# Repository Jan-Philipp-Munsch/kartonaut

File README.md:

# Kartonaut

**A cardboard model rocket that steers its own motor.** *Karton* is German for cardboard: the airframe
is a 75 mm cardboard tube, the motor sits in a servo-driven gimbal, and a home-designed flight computer
holds the rocket upright during the burn. Everything from the circuit board to the control gains is
designed, simulated and documented in this repository.

*Deutsche Fassung: [README.de.md](README.de.md) · detailed documents are in German · last updated: 10 Nov 2026*

<table>
<tr>
<td width="50%"></td>
<td width="50%"><br><br>
<b>Flight computer rev B1 has arrived.</b> Left: the board as delivered on 5 Nov 2026, machine-assembled
with 106 parts. Above: the same board as rendered from the KiCad project, which is generated entirely
from a Python description of the circuit. Next step: hand-soldering the Teensy sockets, connectors and
radio, then the bench test.</td>
</tr>
</table>

## From breakout stack to circuit board

**Before:** the first flight computer was a Teensy 4.1 with breakout boards on a printed ring stack,
held together by threaded rods and jumper wires. On it the core functions were proven on the bench:
IMU and gyro offsets, barometer with Kalman altitude, power measurement, SD logging with CSV export,
radio telemetry to the ground, servo control and a pyro channel that fired a test ejection.

**Now:** the mainboard rev B1 carries the same functions on one 54 × 120 mm board, with newer chips:

- **No loose wires.** Plug-in jumper wires were the biggest failure risk in flight; now everything is
  soldered or on locking JST connectors.
- **IMU exactly on the roll axis**, all flight sensors on a fast SPI bus instead of a shared I²C bus.
- **Safe power:** mechanical main switch with FET load switches, a polyfuse per battery, power monitor
  with a Kelvin shunt, charging inside the rocket.
- **LoRa instead of HC-12** for range, plus magnetometer, GPS socket and microSD on board.
- **Room for later flights:** four pyro channels, a fourth servo, a high-g accelerometer footprint and
  a stacking connector.
- **Lighter and smaller:** a printed sled replaces the ring stack, which helped bring the rocket to 704 g.

<br clear="left">

## At a glance

| | *Kartonaut 1* (first flight) |
|---|---|
| Airframe | cardboard tube Ø 75 mm in three screwed modules, 731 mm long, 3D-printed internals |
| Mass | **704 g** lift-off (mass budget, [`cad/mass_stand2b.md`](cad/mass_stand2b.md)), thrust-to-weight 1.7 |
| Motor | TSP E12 (24 mm, 39 Ns, 3.5 s burn) in a two-axis gimbal with 2 × FrSky W5652H servos |
| Flight computer | Teensy 4.1 on a custom 4-layer board: IMU, barometer, magnetometer, power monitor, LoRa 433 MHz, SD, four pyro channels |
| Control | gyro quaternion, PID on pitch and yaw, gains from Bayesian optimisation in a 6DOF simulation |
| Recovery | CO₂ cartridge pushes off the nose cone, 125 cm parachute |
| Predicted flight | about 74 m apogee, tilt below 2.5° during the burn (simulation, no drag) |

## Status

**Done**

- **Gimbal** with both servos built; tubes A and B of the airframe built.
- **Mainboard rev B1** designed as code (Python → KiCad, four layers, DRC clean), reviewed, ordered
  from JLCPCB on 26 Oct and **delivered on 5 Nov 2026**.
- **6DOF simulation** in Python: thrust curve, identified servo dynamics, sensor noise, Monte Carlo;
  it cut the rocket from 981 g to 704 g and found gains that keep the gimbal off its stop.
- **Flight firmware** (state machine, attitude, Kalman altitude, pyro, telemetry, watchdog) and a
  bench-test console for the board, tested in software-in-the-loop against the simulation.
- **Build manual** with drawings and 1:1 drilling templates; launch stand, TVC test rig and the radio
  bridge of the ground station designed in parametric CAD.
- CI on GitHub Actions for firmware, simulation and pin check against the board.

**In review**

- [PR #9](https://github.com/Jan-Philipp-Munsch/kartonaut/pull/9): soldering and measurement guide for
  rev B1, test firmware for the fitted IMU, flight firmware at 250 Hz with PSRAM log and flash flight
  recorder, LoRa antenna build guide.
- [PR #8](https://github.com/Jan-Philipp-Munsch/kartonaut/pull/8): on-board motor ignition through
  pyro 1, triggered by an authenticated radio command from a laptop.

**Next**

1. Hand-solder the board and bench-test it with `revb_test` (power monitor and one resistor follow
   with the second DigiKey shipment).
2. Print and weigh the parts, assemble the rocket, balance the centre of gravity.
3. Ground tests: servo-to-gimbal ratio, CO₂ ejection, TVC test rig with a propeller motor, radio range.
4. ***Kartonaut 1*: controlled ascent on one motor, parachute recovery.**

Details and changelog in [PROJECT.md](PROJECT.md), build log in [docs/BUILD.md](docs/BUILD.md).

## Gallery

<table>
<tr>
<td align="center" width="33%"><br><sub>Section through <i>Kartonaut 1</i>: gimbal, avionics, CO₂ and parachute</sub></td>
<td align="center" width="33%"><br><sub>Push-rod gimbal with two servos, built</sub></td>
<td align="center" width="33%"><br><sub>Avionics module: board on a printed sled</sub></td>
</tr>
<tr>
<td align="center"><br><sub>TVC test rig: a propeller replaces the motor</sub></td>
<td align="center"><br><sub>Launch stand on three adjustable legs</sub></td>
<td align="center"><br><sub>Radio bridge with half-wave dipole</sub></td>
</tr>
<tr>
<td align="center" colspan="2"><br><sub>Simulation: old gains (gimbal saturated) against tuned gains</sub></td>
<td align="center"><br><sub>Overview drawing from the build manual</sub></td>
</tr>
</table>

## What is inside

| Part | What it does | Where |
|---|---|---|
| Mainboard | KiCad project generated from `circuit.py`: schematic, layout, Gerber/BOM/CPL, datasheet | [hardware/mainboard/](hardware/mainboard/README.md) |
| Simulation | Python 6DOF model `tvcsim` with the firmware controller ported 1:1, gain tuning, landing studies | [simulation/](simulation/README.md) |
| Firmware | PlatformIO for Teensy 4.1: flight software, sensor drivers, bench-test console, native tests | [firmware/](firmware/README.md) |
| Mechanics | parametric CAD for printed parts, launch stand, test rig; mass and inertia models | [cad/](cad/README.md) |
| Build manual | modules, parts list, build steps, cable plan ([PDF](docs/bauanleitung/Bauanleitung_Kartonaut1.pdf)) | [docs/Bauanleitung_Kartonaut1.md](docs/Bauanleitung_Kartonaut1.md) |
| Ground system | launch protocol, radio bridge, ESP32 station as later option | [groundstation/](groundstation/README.md) |
| Experiments | ready-to-run ground tests | [docs/experiments/](docs/experiments/README.md) |

```bash
cd simulation && python -m pytest tests            # simulation tests
cd firmware && pio test -e native                  # firmware tests without hardware
cd firmware && pio run -e teensy41_revb            # flight firmware for rev B1
MS_CONFIG=erstflug python cad/modular.py           # printed parts, mass, renders
```

## Background

Inspired by the "Scout F" of [BPS.space](https://bps.space). Later flights may get landing legs, a
landing burn on a second motor and roll control; the board already has room for them. The old ground
station lives in [kartonaut-ground](https://github.com/Jan-Philipp-Munsch/kartonaut-ground).

## License

[MIT](LICENSE). The BPS.space Scout F files that served as reference are not part of this repository.

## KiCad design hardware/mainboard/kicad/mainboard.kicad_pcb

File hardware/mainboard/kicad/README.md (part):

# Mainboard rev B1 – KiCad-Projekt

Stand 2026-10-22. Schaltplan und Platine werden hier **aus Code erzeugt**, nicht von Hand gezeichnet.
Die Quelle der Wahrheit ist `circuit.py`: Schaltplan, Platine und Prüfungen werden daraus abgeleitet.
Die Vorgabe ist die Spezifikation `../README.md`, Stand B1: rev B plus Review A1 bis A8
(`../review_kicad_2026-10-21.md`) und die Entscheidungen E1 bis E10 (`../Komponenten_2026-10-22.md`).
Dieses Dokument beschreibt, wie das Projekt entstanden ist, was fertig ist, was offen ist und wo bewusst
von der Spezifikation abgewichen wurde. Die Fertigerwahl steht in `../Fertiger_2026-10-21.md`.

## 1. Stand auf einen Blick

| Schritt | Stand |
|---|---|
| Schaltung als Daten (`circuit.py`) | 174 Bauteile (12 davon DNP), 114 Netze, 7 Schaltplanblätter |
| ERC | **0 Fehler, 0 Warnungen**, 4 begründete Ausschlüsse (§6) |
| Netzliste gegen Spezifikation §4 (`check_design.py`) | **OK**: 39 Teensy-Pins, 7 Chip-Selects, 7 Mux-Kanäle, 11 Schienen, Kelvin-Abgriff |
| Platzierung | **alle 174 Footprints**, keine Überschneidung; die drei Sensoren vom 23.10. mit `add_parts.py` nachgesetzt |
| Strompfade | 2S-Pfad, Pyro-Ausgänge und VSYS_IN als F.Cu-Flächen (§5.4); kein 2S-Netz auf In2 |
| Routing | 3145 Bahnsegmente, 469 Vias, vier Lagen (Stand 24.10.); `./make.sh pcb` braucht etwa 25 Minuten, danach `close_gaps.py` (§5.5) |
| DRC (JLC-Regeln) | **0 Fehler**, Schaltplan-Parität **0 Abweichungen** |
| Offene Verbindungen | **0** (23.10., nach Handrouting und Skript-Router) |
| Abbildungen | Renders oben, unten und schräg, Lagenbilder (`img/`) |
| Rundgang | `RUNDGANG_PLATINE.pdf`: Anleitung mit Bildern zu Aufbau, Lagen, Strompfaden, Vias und DRC (`guide_dump.py`, `make_guide.py`) |
| Fertigungsdaten (Gerber, BOM, CPL) | `./make.sh fab` → `fab/`, Stand 23.10. mit den drei Sensoren (§8) |

| Oben | Unten |
|---|---|
|  |  |

Die Lagen einzeln: `img/layers.pdf` (F.Cu, In1 GND, In2, B.Cu Versorgung, Bestückungsdruck) und
`img/layer_*.png`.

## 2. Werkzeuge

- **KiCad 10.0.6.** Die winget-Installation für alle Benutzer blieb an der Administrator-Abfrage
  hängen. Deshalb wurde der signierte Installer (KiCad Services Corp.) als Benutzerinstallation
  ausgeführt: `/S /CurrentUser` nach `%LOCALAPPDATA%\Programs\KiCad\10.0`. Die globalen
  Bibliothekstabellen (`sym-lib-table`, `fp-lib-table`) wurden aus dem Template nach
  `%APPDATA%\kicad\10.0\` kopiert; das macht die GUI sonst beim ersten Start.
- **easyeda2kicad** (pip) für die Teile, die nicht in der KiCad-Bibliothek sind: LSM6DSV16X (C5267406, Symbol; der Footprint ist der des ICM-42688-P C1850418, gleiches Land-Pattern),
  BMP390 (C5124834), TPS63070RNMR (C109322) und E22-400T22S (C2903765). Symbol, Footprint und
  3D-Modell kommen direkt aus der LCSC/EasyEDA-Datenbank, also genau die Footprints, mit denen JLC bestückt.
- **Freerouting 2.5.0** als JAR mit einer portablen **Temurin-25-JRE** (Zip, keine Installation), beides
  unter `%LOCALAPPDATA%\Programs\freerouting\`, Prüfsummen kontrolliert. Die native
  `freerouting-cli.exe` derselben Version stürzt mit einem GraalVM-Fehler ab; die JAR braucht Java 25.
- **CadQuery** für zwei 3D-Modelle, die fehlen: Teensy 4.1 (vereinfacht, auf 8,5-mm-Sockeln) und
  XT30PW-M (die KiCad-Bibliothek nennt das Modell, liefert es aber nicht).
- Datenblätter für die eigenen Entscheidungen: TPS63070 (SLVSC58B: Pinbelegung, Teiler-Tabelle 4,
  Kondensatoren), ICM-42688-P (DS-000347) und LSM6DSV16X (AN5763 Tab. 1: Pins 9–11 offen, 2–3 an GND).

## 3. Aufbau und Ablauf

```
circuit.py          Schaltung als Daten: Bauteile, Werte, Footprints, LCSC-Nummern, Netze, Blätter, Blöcke, Netzklassen
build_lib.py        lib/mainboard.*: Teensy-Symbol, INA239-Symbol, Sockel-Footprint, Kelvin-Shunt-Footprint
                    R_2512_Kelvin, 3D-Modelle Teensy und XT30; Pin-Typen der LCSC-Symbole
gen_schematic.py    Projektdatei (JLC-Regeln, Netzklassen, ERC-Ausschlüsse), Wurzelblatt und 7 Unterblätter
check_design.py     Tor 1: Netzliste aus dem Schaltplan gegen die Pin-Tabelle der Spezifikation
gen_pcb.py          Platine: Umriss, Footprints, Platzierung, Flächen, Sperrflächen, Plane-Vias, DSN-Export, SES-Übernahme, Nachbesserung,
                    Bestückungsdruck (`gen_pcb.py silk`: nur der Druck, auf der gerouteten Platine)
logo.py             Kartonaut-Abzeichen als Polygone, für den Bestückungsdruck und docs/brand/*.svg
render.py           Lagenbilder zuschneiden und zusammenfügen, Renders auf die Platine zuschneiden
make.sh             ganze Kette: ./make.sh [sch|pcb|drc|img|fab]
fab.py              `./make.sh fab`: Bestelldateien für JLCPCB nach fab/ (Gerber/Bohrdaten als ZIP, BOM, CPL, FAB.md)
widen.py            verbreitert schmale Versorgungsstücke, soweit der DRC es zulässt (nach dem Handrouting)
add_parts.py        setzt neue Bauteile aus circuit.py an feste Positionen in die fertige Platine (Netze, Blattpfad, DNP),
                    räumt fremdes Kupfer unter ihren Pads weg; danach close_gaps.py / route_gaps.py
snapshot.py         schnelles Bild einzelner Lagen beim Entwickeln
gaps.py             die offenen Verbindungen aus out/drc.json: was, wo, wie weit; `gaps.py png` mit Bild je Häufung
close_gaps.py       `dump`: Geometrie der Platine und die offenen Verbindungen nach out/geom.json; `apply`: Ergebnis des
                    Gitter-Routers in die Platine (KiCad-Python)
route_gaps.py       Gitter-Router (System-Python mit numpy/scipy): A* auf 0,05 mm, F.Cu/In2 mit Vias, Rip-up von
                    Signalbahnen; `debug n` mit Bild und Kennzahlen je Lücke, `region x0 y0 x1 y1` reißt einen Bereich auf
lib/                lcsc.* (easyeda2kicad), mainboard.* (eigene)
out/                Schaltplan-PDF, ERC- und DRC-Bericht (alles andere dort ist Zwischenstand)
img/                Renders und Lagenbilder
fab/                Bestelldateien (ZIP, BOM, CPL, FAB.md); fab/gerber/ ist der ungepackte Zwischenstand
```

Neu erzeugen (Git Bash):

```bash
./make.sh
```

`make.sh` ruft `kicad-cli` aus der Bash auf und nicht aus Python. Aus der Microsoft-Store-Python gestartet,
findet `kicad-cli` die globalen Bibliothekstabellen nicht, denn der App-Container der Store-Python
verdeckt sie. Der ERC meldet dann 265 Bibliotheksfehler, und die Renders haben keine Modelle.

Warum Code statt GUI: Schaltung, Schaltplan und Platine können nicht auseinanderlaufen, jede Änderung ist
ein Diff in `circuit.py`, und ERC, Netzlistenprüfung und DRC laufen auf Knopfdruck. Die Dateien lassen sich
normal in KiCad öffnen. Sobald dort von Hand geroutet wird (§5.4), ist die Platinendatei die Quelle und
`./make.sh pcb` darf nicht mehr laufen. `./make.sh sch` und `./make.sh drc` bleiben nutzbar.

## 4. Schaltplan

Jedes Pin bekommt einen kurzen Draht und ein globales Netzlabel. So sind die Netznamen in Netzliste,
Platine, Netzklassen und Spezifikation dieselben (`VSERVO`, nicht `/Versorgung/VSERVO`). Jedes Blatt
ist in umrahmte Funktionsblöcke gegliedert. Die Blätter heißen Versorgung, Teensy, Sensorik, Funk,
Aktoren, Pyro und Signal. Die UUIDs werden aus Blatt und Referenz berechnet und sind deshalb bei jedem
Lauf gleich. PDF: `out/mainboard_schematic.pdf`.

## 5. Platine

### 5.1 Lagen

| Lage | Inhalt |
|---|---|
| F.Cu | alle Bauteile, Signale, GND-Füllung |
| In1.Cu | **durchgehende GND-Fläche** (Lagentyp *power*, wird nicht geroutet) |
| In2.Cu | Signale, GND-Füllung |
| B.Cu | **geteilte Versorgungsfläche**: GND_PWR unter allem, was am 2S hängt (TVC-Band mit XT30 und Servos, Mitte unter den VSERVO-Puffern, rechter Streifen mit den Aktoren, äußerer rechter Streifen neben J_STACK, Spitzen-Band unter Pyro, Arming und Summer); **5V_SYS** unter der 1S-Seite (linker Streifen, unter dem Teensy) |

Die Spezifikation sah die Versorgungsflächen auf Lage 3 vor. B.Cu ist gleichwertig und trägt ohnehin
keine Bauteile. In2 bleibt so als zweite Signallage frei; ohne sie war die Platine nicht zu entflechten.
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
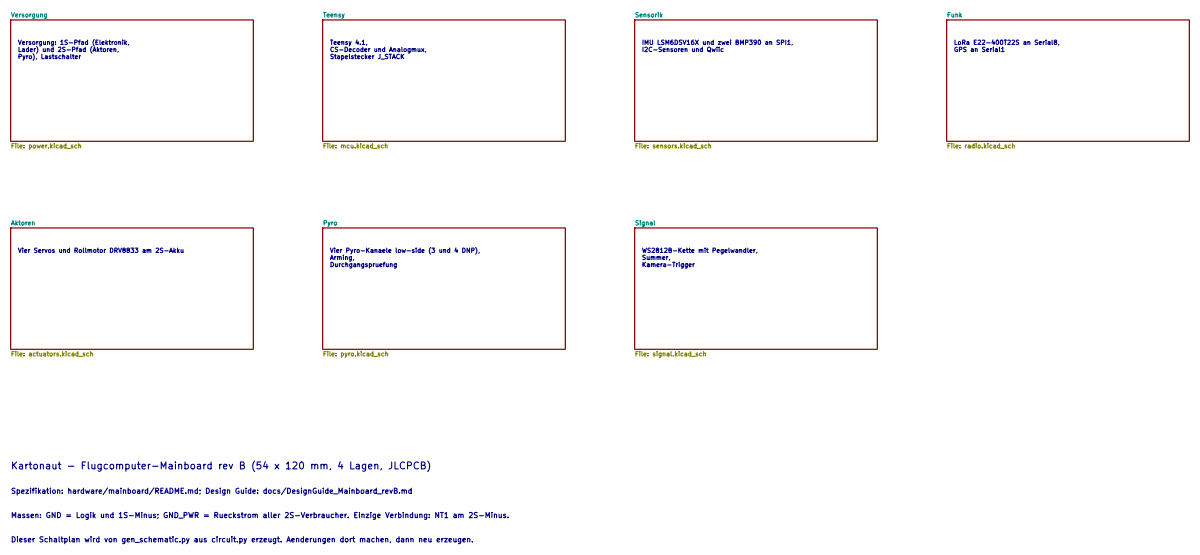
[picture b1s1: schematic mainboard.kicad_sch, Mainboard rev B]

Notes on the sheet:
Versorgung: 1S-Pfad (Elektronik, Lader) und 2S-Pfad (Aktoren, Pyro), Lastschalter
Teensy 4.1, CS-Decoder und Analogmux, Stapelstecker J_STACK
IMU LSM6DSV16X und zwei BMP390 an SPI1, I2C-Sensoren und Qwiic
LoRa E22-400T22S an Serial8, GPS an Serial1
Vier Servos und Rollmotor DRV8833 am 2S-Akku
Vier Pyro-Kanaele low-side (3 und 4 DNP), Arming, Durchgangspruefung
WS2812B-Kette mit Pegelwandler, Summer, Kamera-Trigger
Kartonaut - Flugcomputer-Mainboard rev B (54 x 120 mm, 4 Lagen, JLCPCB)
Spezifikation: hardware/mainboard/README.md; Design Guide: docs/DesignGuide_Mainboard_revB.md
Massen: GND = Logik und 1S-Minus; GND_PWR = Rueckstrom aller 2S-Verbraucher. Einzige Verbindung: NT1 am 2S-Minus.
Dieser Schaltplan wird von gen_schematic.py aus circuit.py erzeugt. Aenderungen dort machen, dann neu erzeugen.

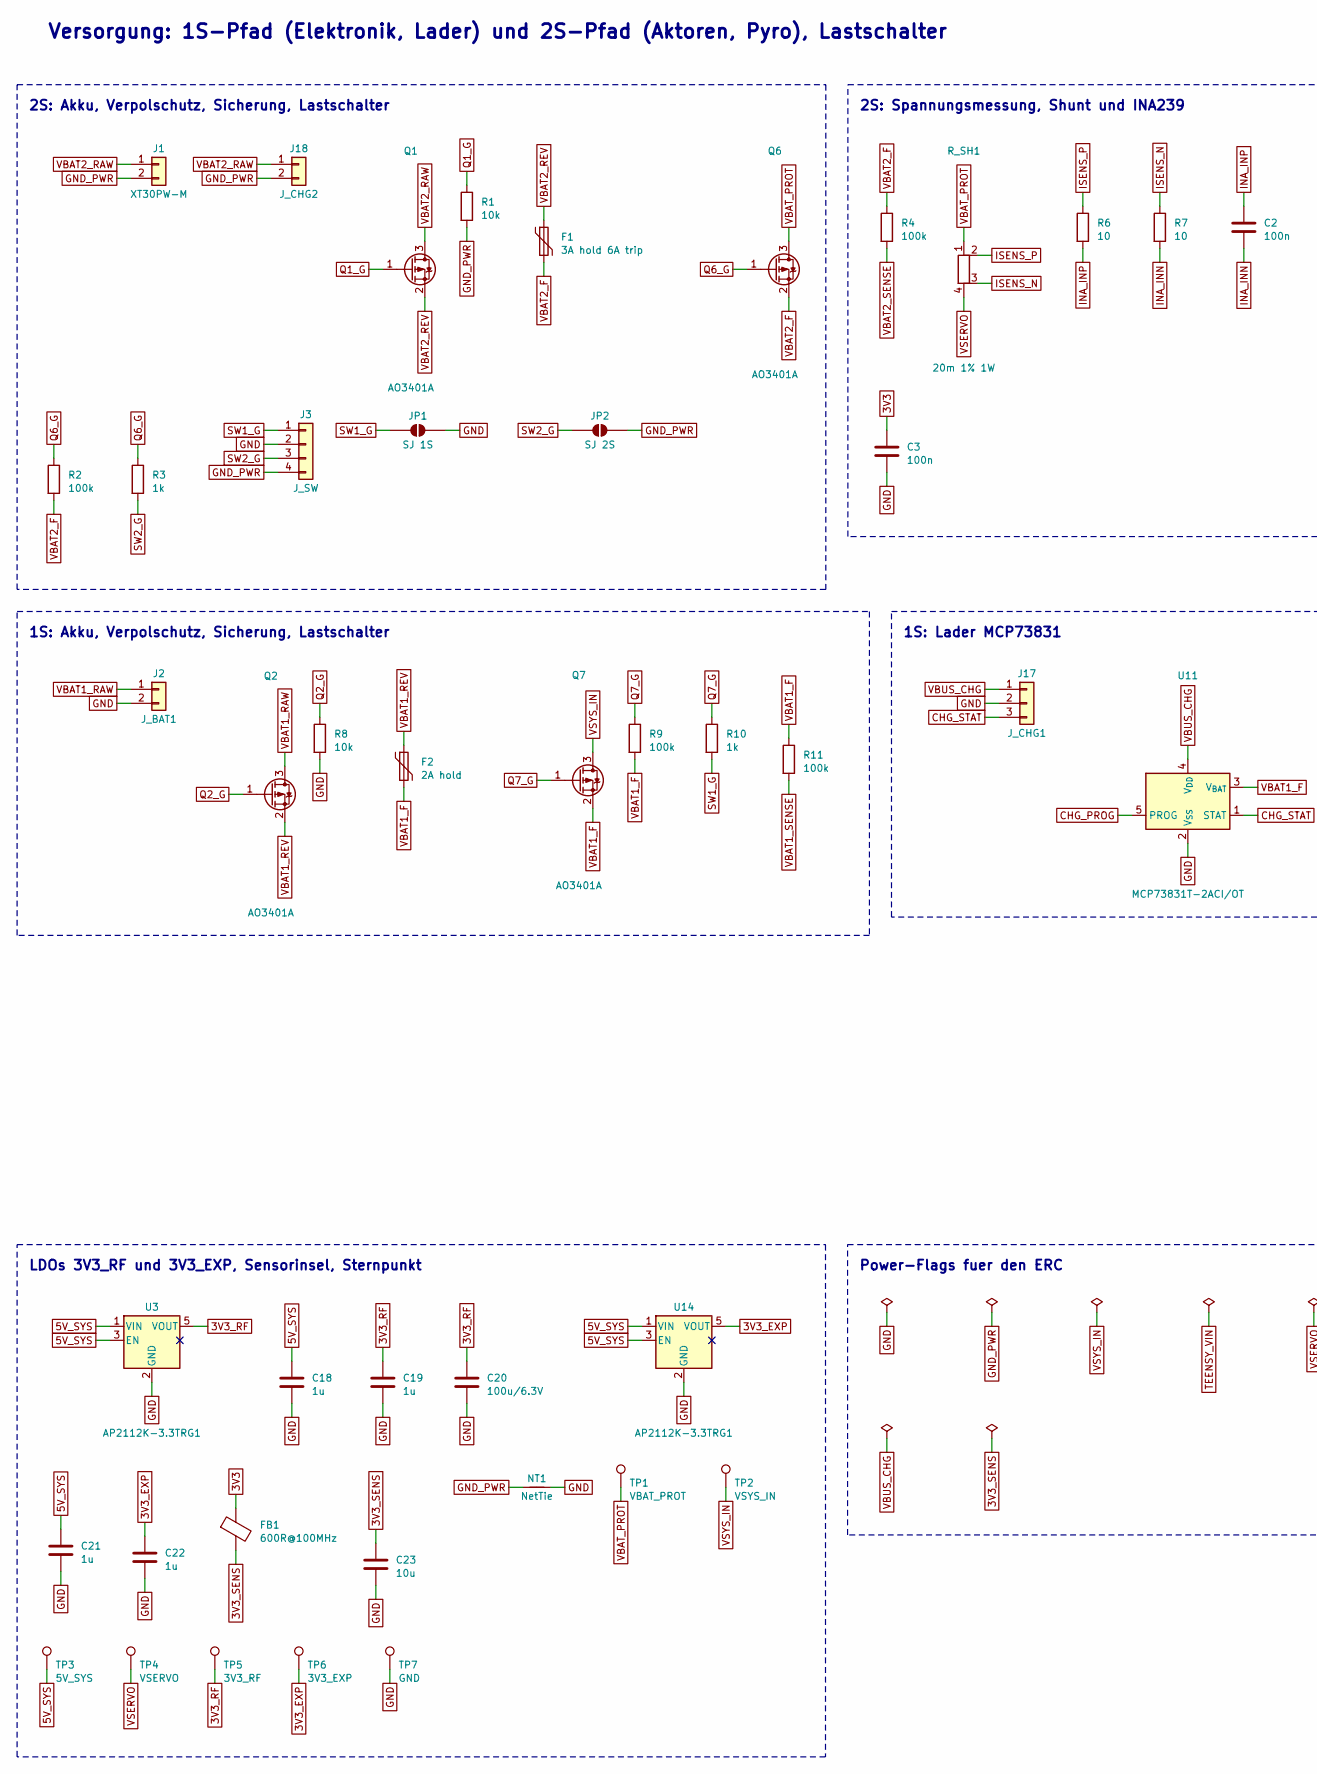
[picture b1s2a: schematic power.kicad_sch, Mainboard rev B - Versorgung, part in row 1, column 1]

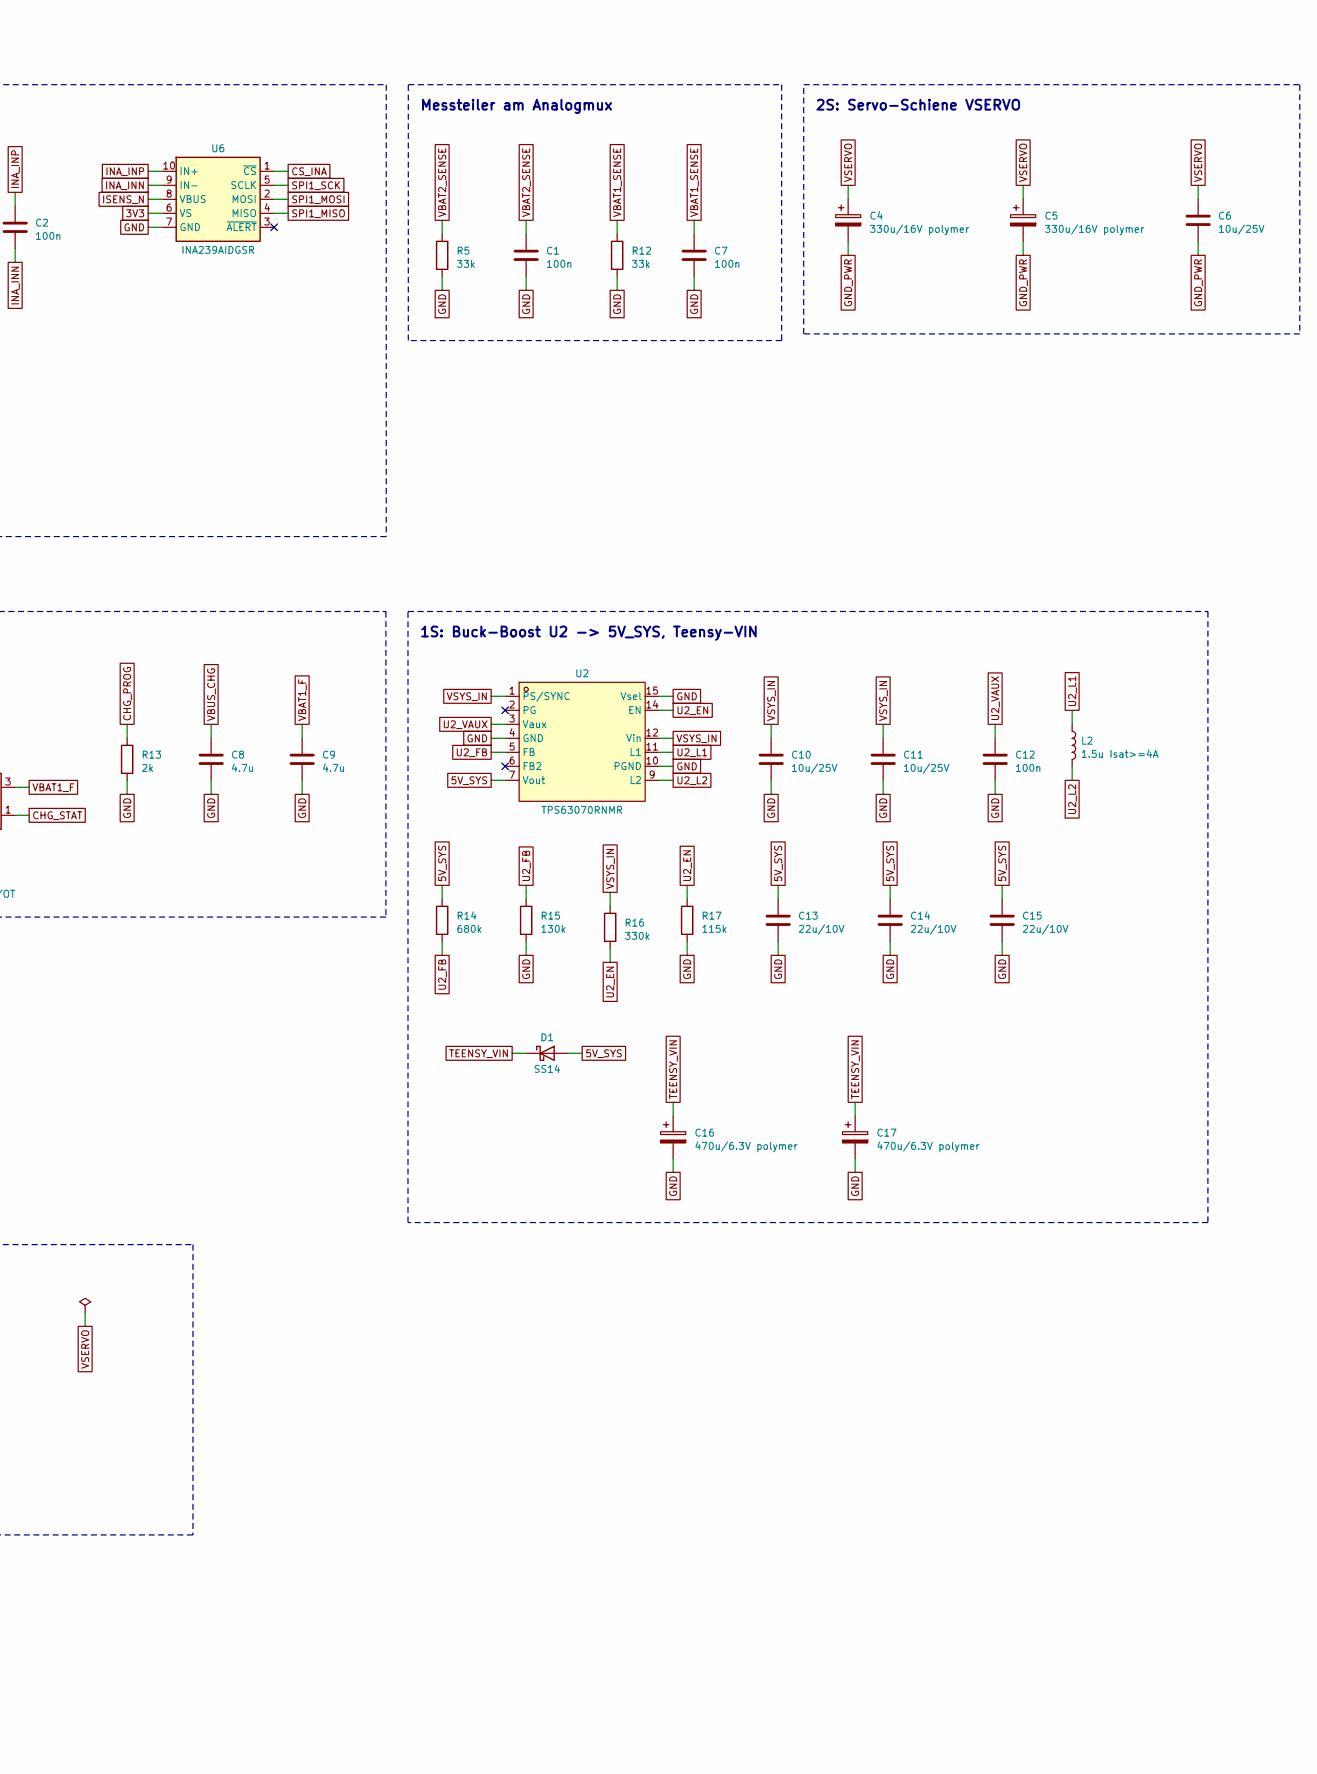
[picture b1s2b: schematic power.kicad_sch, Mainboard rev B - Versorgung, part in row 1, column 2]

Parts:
C1, C2, C3, C7, C12: 100n; C_0603_1608Metric
C4, C5: 330u/16V polymer; CP_EIA-7343-31_Kemet-D
C6, C10, C11: 10u/25V; C_0805_2012Metric
C8, C9: 4.7u; C_0805_2012Metric
C13, C14, C15: 22u/10V; C_0805_2012Metric
C16, C17: 470u/6.3V polymer; CP_EIA-7343-31_Kemet-D
C18, C19, C21, C22: 1u; C_0603_1608Metric
C20: 100u/6.3V; C_1210_3225Metric
C23: 10u; C_0805_2012Metric
D1: SS14; D_SMA; LCSC C2480
F1: 3A hold 6A trip; Fuse_1812_4532Metric
F2: 2A hold; Fuse_1812_4532Metric
FB1: 600R@100MHz; L_0603_1608Metric
J1: XT30PW-M; AMASS_XT30PW-M_1x02_P2.50mm_Horizontal
J2: J_BAT1; JST_PH_B2B-PH-K_1x02_P2.00mm_Vertical
J3: J_SW; JST_PH_B4B-PH-K_1x04_P2.00mm_Vertical
J17: J_CHG1; JST_PH_B3B-PH-K_1x03_P2.00mm_Vertical
J18: J_CHG2; JST_PH_B2B-PH-K_1x02_P2.00mm_Vertical
JP1: SJ 1S; SolderJumper-2_P1.3mm_Open_RoundedPad1.0x1.5mm
JP2: SJ 2S; SolderJumper-2_P1.3mm_Open_RoundedPad1.0x1.5mm
L2: 1.5u Isat>=4A; L_Changjiang_FNR5040S
NT1: NetTie; NetTie-2_SMD_Pad0.5mm
Q1, Q2, Q6, Q7: AO3401A; SOT-23; LCSC C15127
R1, R8: 10k; R_0603_1608Metric
R2, R4, R9, R11: 100k; R_0603_1608Metric
R3, R10: 1k; R_0603_1608Metric
R5, R12: 33k; R_0603_1608Metric
R6, R7: 10; R_0603_1608Metric
R13: 2k; R_0603_1608Metric
R14: 680k; R_0603_1608Metric
R15: 130k; R_0603_1608Metric
R16: 330k; R_0603_1608Metric
R17: 115k; R_0603_1608Metric
R_SH1: 20m 1% 1W; R_2512_Kelvin
TP1: VBAT_PROT; TestPoint_Pad_D1.5mm
TP2: VSYS_IN; TestPoint_Pad_D1.5mm
TP3: 5V_SYS; TestPoint_Pad_D1.5mm
TP4: VSERVO; TestPoint_Pad_D1.5mm
TP5: 3V3_RF; TestPoint_Pad_D1.5mm
TP6: 3V3_EXP; TestPoint_Pad_D1.5mm
TP7: GND; TestPoint_Pad_D1.5mm
U2: TPS63070RNMR; VQFN-15_L3.0-W2.5-P0.50-BL; LCSC C109322
U3, U14: AP2112K-3.3TRG1; SOT-23-5; LCSC C51118
U6: INA239AIDGSR; MSOP-10_3x3mm_P0.5mm
U11: MCP73831T-2ACI/OT; SOT-23-5; LCSC C424093

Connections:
3V3: C3.1, FB1.1, U6.6 (VS); also elsewhere on the board
3V3_EXP: C22.1, TP6.1, U14.5 (VOUT); also elsewhere on the board
3V3_RF: C19.1, C20.1, TP5.1, U3.5 (VOUT); also elsewhere on the board
3V3_SENS: C23.1, FB1.2; also elsewhere on the board
5V_SYS: C13.1, C14.1, C15.1, C18.1, C21.1, D1.2 (A), R14.1, TP3.1, U2.7 (Vout), U3.1 (VIN), U3.3 (EN), U14.1 (VIN), U14.3 (EN); also elsewhere on the board
CHG_PROG: R13.1, U11.5 (PROG)
CHG_STAT: J17.3, U11.1 (STAT)
CS_INA: U6.1 (~CS); also elsewhere on the board
GND: C1.2, C3.2, C7.2, C8.2, C9.2, C10.2, C11.2, C12.2, C13.2, C14.2, C15.2, C16.2, C17.2, C18.2, C19.2, C20.2, C21.2, C22.2, C23.2, J2.2, J3.2, J17.2, JP1.2 (B), NT1.2, R5.2, R8.2, R12.2, R13.2, R15.2, R17.2, TP7.1, U2.4 (GND), U2.10 (PGND), U2.15 (Vsel), U3.2 (GND), U6.7 (GND), U11.2 (V_{SS}), U14.2 (GND); also elsewhere on the board
GND_PWR: C4.2, C5.2, C6.2, J1.2, J3.4, J18.2, JP2.2 (B), NT1.1, R1.2; also elsewhere on the board
INA_INN: C2.2, R7.2, U6.9 (IN-)
INA_INP: C2.1, R6.2, U6.10 (IN+)
ISENS_N: R7.1, R_SH1.3, U6.8 (VBUS)
ISENS_P: R6.1, R_SH1.2
Q1_G: Q1.1 (G), R1.1
Q2_G: Q2.1 (G), R8.1
Q6_G: Q6.1 (G), R2.1, R3.1
Q7_G: Q7.1 (G), R9.1, R10.1
SPI1_MISO: U6.4 (MISO); also elsewhere on the board
SPI1_MOSI: U6.2 (MOSI); also elsewhere on the board
SPI1_SCK: U6.5 (SCLK); also elsewhere on the board
SW1_G: J3.1, JP1.1 (A), R10.2
SW2_G: J3.3, JP2.1 (A), R3.2
TEENSY_VIN: C16.1, C17.1, D1.1 (K); also elsewhere on the board
U2_EN: R16.2, R17.1, U2.14 (EN)
U2_FB: R14.2, R15.1, U2.5 (FB)
U2_L1: L2.1, U2.11 (L1)
U2_L2: L2.2, U2.9 (L2)
U2_VAUX: C12.1, U2.3 (Vaux)
VBAT1_F: C9.1, F2.2, Q7.2 (S), R9.2, R11.1, U11.3 (V_{BAT})
VBAT1_RAW: J2.1, Q2.3 (D)
VBAT1_REV: F2.1, Q2.2 (S)
VBAT1_SENSE: C7.1, R11.2, R12.1; also elsewhere on the board
VBAT2_F: F1.2, Q6.2 (S), R2.2, R4.1
VBAT2_RAW: J1.1, J18.1, Q1.3 (D)
VBAT2_REV: F1.1, Q1.2 (S)
VBAT2_SENSE: C1.1, R4.2, R5.1; also elsewhere on the board
VBAT_PROT: Q6.3 (D), R_SH1.1, TP1.1; also elsewhere on the board
VBUS_CHG: C8.1, J17.1, U11.4 (V_{DD})
VSERVO: C4.1, C5.1, C6.1, R_SH1.4, TP4.1; also elsewhere on the board
VSYS_IN: C10.1, C11.1, Q7.3 (D), R16.1, TP2.1, U2.1 (PS/SYNC), U2.12 (Vin)

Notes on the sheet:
Versorgung: 1S-Pfad (Elektronik, Lader) und 2S-Pfad (Aktoren, Pyro), Lastschalter
2S: Akku, Verpolschutz, Sicherung, Lastschalter
2S: Spannungsmessung, Shunt und INA239
Messteiler am Analogmux
2S: Servo-Schiene VSERVO
1S: Akku, Verpolschutz, Sicherung, Lastschalter
1S: Lader MCP73831
1S: Buck-Boost U2 -> 5V_SYS, Teensy-VIN
LDOs 3V3_RF und 3V3_EXP, Sensorinsel, Sternpunkt
Power-Flags fuer den ERC

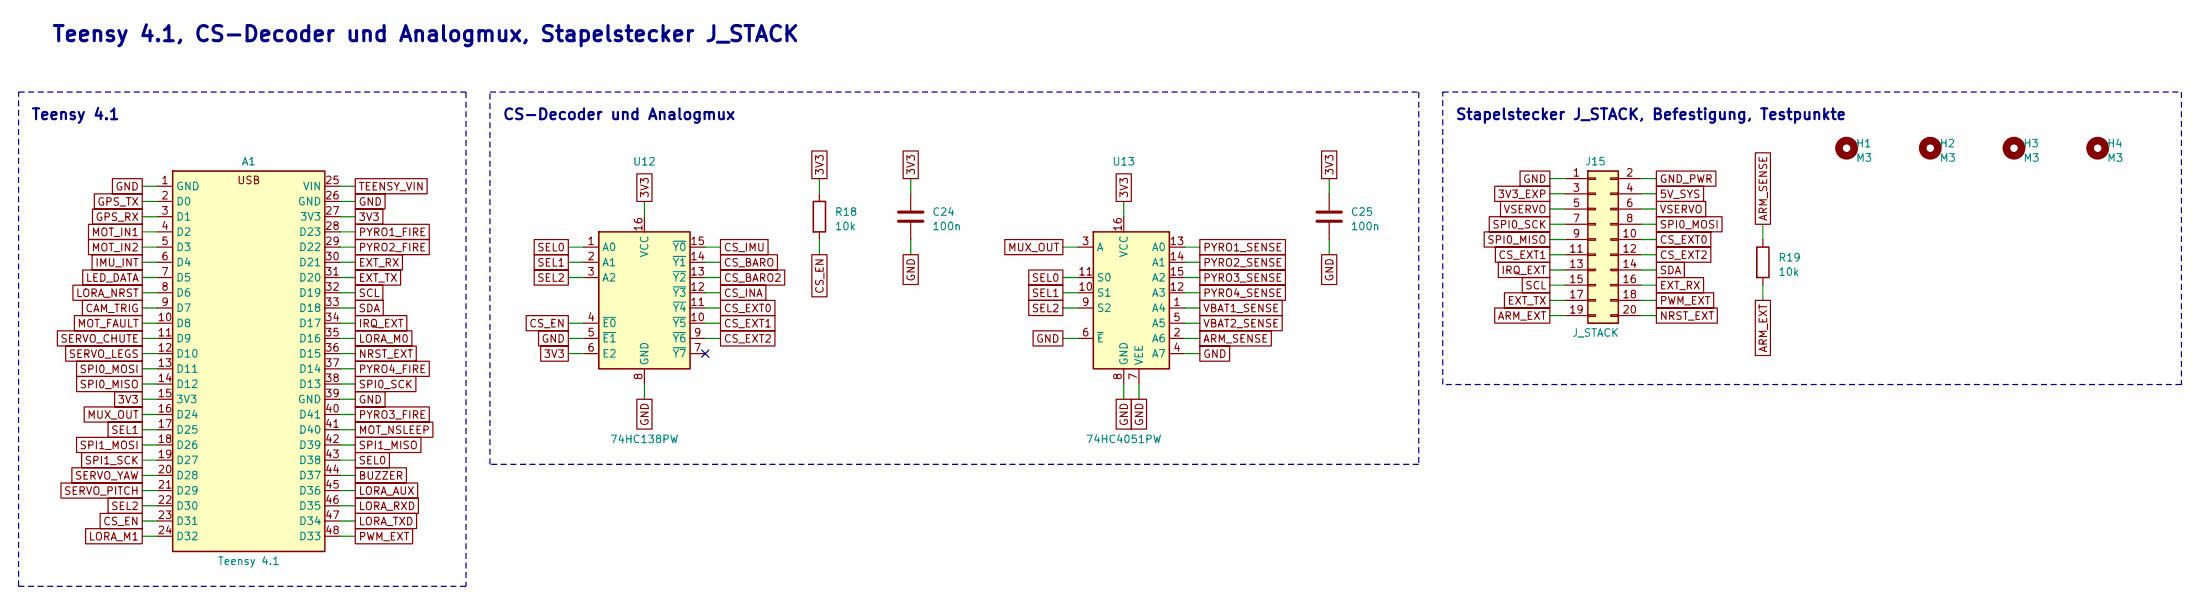
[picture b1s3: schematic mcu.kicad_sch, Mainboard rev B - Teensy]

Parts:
A1: Teensy 4.1; Teensy41_Socket
C24, C25: 100n; C_0603_1608Metric
H1, H2, H3, H4: M3; MountingHole_3.2mm_M3
J15: J_STACK; PinHeader_2x10_P2.54mm_Vertical
R18, R19: 10k; R_0603_1608Metric
U12: 74HC138PW; TSSOP-16_4.4x5mm_P0.65mm
U13: 74HC4051PW; TSSOP-16_4.4x5mm_P0.65mm

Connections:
3V3: A1.15 (3V3), A1.27 (3V3), C24.1, C25.1, R18.1, U12.6 (E2), U12.16 (VCC), U13.16 (VCC); also elsewhere on the board
3V3_EXP: J15.3; also elsewhere on the board
5V_SYS: J15.4; also elsewhere on the board
ARM_EXT: J15.19, R19.2
ARM_SENSE: R19.1, U13.2 (A6); also elsewhere on the board
BUZZER: A1.44 (D37); also elsewhere on the board
CAM_TRIG: A1.9 (D7); also elsewhere on the board
CS_BARO: U12.14 (~Y1); also elsewhere on the board
CS_BARO2: U12.13 (~Y2); also elsewhere on the board
CS_EN: A1.23 (D31), R18.2, U12.4 (~E0)
CS_EXT0: J15.10, U12.11 (~Y4)
CS_EXT1: J15.11, U12.10 (~Y5)
CS_EXT2: J15.12, U12.9 (~Y6)
CS_IMU: U12.15 (~Y0); also elsewhere on the board
CS_INA: U12.12 (~Y3); also elsewhere on the board
EXT_RX: A1.30 (D21), J15.16
EXT_TX: A1.31 (D20), J15.17
GND: A1.1 (GND), A1.26 (GND), A1.39 (GND), C24.2, C25.2, J15.1, U12.5 (~E1), U12.8 (GND), U13.4 (A7), U13.6 (~E), U13.7 (VEE), U13.8 (GND); also elsewhere on the board
GND_PWR: J15.2; also elsewhere on the board
GPS_RX: A1.3 (D1); also elsewhere on the board
GPS_TX: A1.2 (D0); also elsewhere on the board
IMU_INT: A1.6 (D4); also elsewhere on the board
IRQ_EXT: A1.34 (D17), J15.13
LED_DATA: A1.7 (D5); also elsewhere on the board
LORA_AUX: A1.45 (D36); also elsewhere on the board
LORA_M0: A1.35 (D16); also elsewhere on the board
LORA_M1: A1.24 (D32); also elsewhere on the board
LORA_NRST: A1.8 (D6); also elsewhere on the board
LORA_RXD: A1.46 (D35); also elsewhere on the board
LORA_TXD: A1.47 (D34); also elsewhere on the board
MOT_FAULT: A1.10 (D8); also elsewhere on the board
MOT_IN1: A1.4 (D2); also elsewhere on the board
MOT_IN2: A1.5 (D3); also elsewhere on the board
MOT_NSLEEP: A1.41 (D40); also elsewhere on the board
MUX_OUT: A1.16 (D24), U13.3 (A)
NRST_EXT: A1.36 (D15), J15.20
PWM_EXT: A1.48 (D33), J15.18
PYRO1_FIRE: A1.28 (D23); also elsewhere on the board
PYRO1_SENSE: U13.13 (A0); also elsewhere on the board
PYRO2_FIRE: A1.29 (D22); also elsewhere on the board
PYRO2_SENSE: U13.14 (A1); also elsewhere on the board
PYRO3_FIRE: A1.40 (D41); also elsewhere on the board
PYRO3_SENSE: U13.15 (A2); also elsewhere on the board
PYRO4_FIRE: A1.37 (D14); also elsewhere on the board
PYRO4_SENSE: U13.12 (A3); also elsewhere on the board
SCL: A1.32 (D19), J15.15; also elsewhere on the board
SDA: A1.33 (D18), J15.14; also elsewhere on the board
SEL0: A1.43 (D38), U12.1 (A0), U13.11 (S0)
SEL1: A1.17 (D25), U12.2 (A1), U13.10 (S1)
SEL2: A1.22 (D30), U12.3 (A2), U13.9 (S2)
SERVO_CHUTE: A1.11 (D9); also elsewhere on the board
SERVO_LEGS: A1.12 (D10); also elsewhere on the board
SERVO_PITCH: A1.21 (D29); also elsewhere on the board
SERVO_YAW: A1.20 (D28); also elsewhere on the board
SPI0_MISO: A1.14 (D12), J15.9
SPI0_MOSI: A1.13 (D11), J15.8
SPI0_SCK: A1.38 (D13), J15.7
SPI1_MISO: A1.42 (D39); also elsewhere on the board
SPI1_MOSI: A1.18 (D26); also elsewhere on the board
SPI1_SCK: A1.19 (D27); also elsewhere on the board
TEENSY_VIN: A1.25 (VIN); also elsewhere on the board
VBAT1_SENSE: U13.1 (A4); also elsewhere on the board
VBAT2_SENSE: U13.5 (A5); also elsewhere on the board
VSERVO: J15.5, J15.6; also elsewhere on the board

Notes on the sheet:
Teensy 4.1, CS-Decoder und Analogmux, Stapelstecker J_STACK
Teensy 4.1
CS-Decoder und Analogmux
Stapelstecker J_STACK, Befestigung, Testpunkte

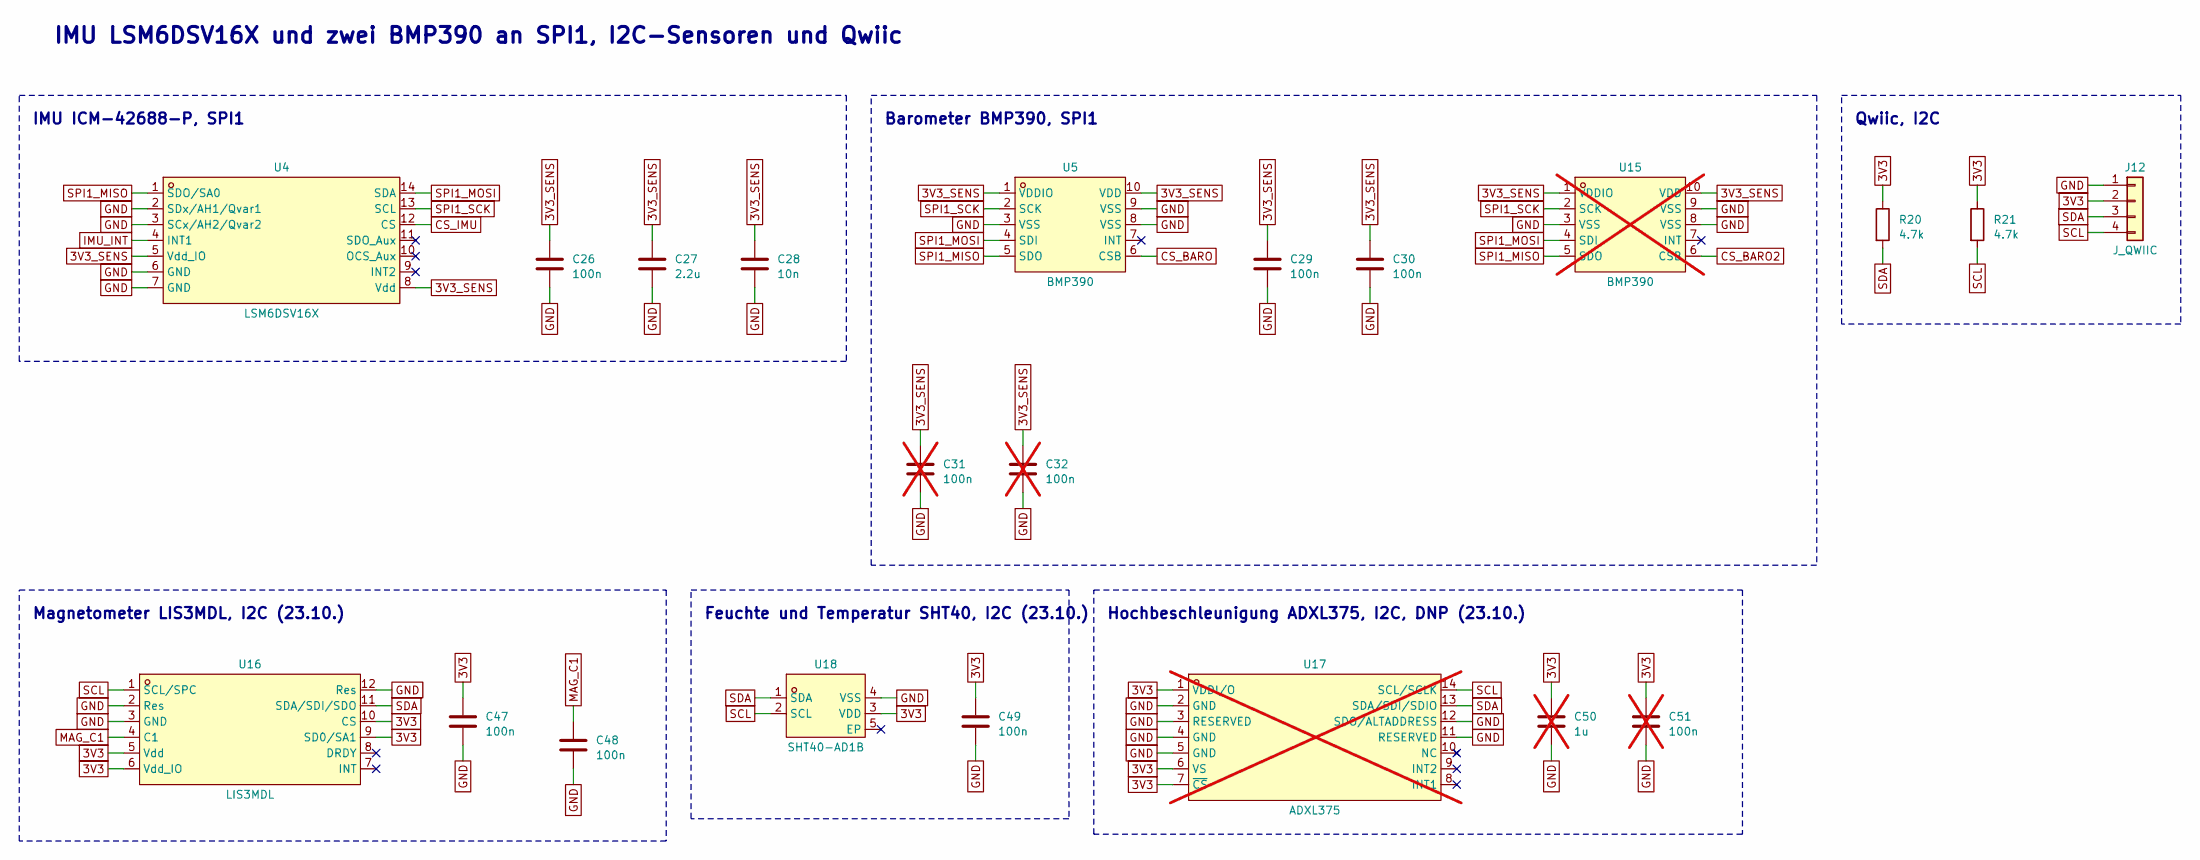
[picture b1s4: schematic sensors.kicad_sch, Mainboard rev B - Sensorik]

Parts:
C26, C29, C30, C47, C48, C49: 100n; C_0603_1608Metric
C27: 2.2u; C_0603_1608Metric
C28: 10n; C_0603_1608Metric
C31, C32, C51: 100n; C_0603_1608Metric; not fitted
C50: 1u; C_0603_1608Metric; not fitted
J12: J_QWIIC; JST_SH_BM04B-SRSS-TB_1x04-1MP_P1.00mm_Vertical
R20, R21: 4.7k; R_0603_1608Metric
U4: LSM6DSV16X; LGA-14_L3.0-W2.5-P0.50-TL; LCSC C5267406
U5: BMP390; LGA-10_L2.0-W2.0-P0.50-BL; LCSC C5124834
U15: BMP390; LGA-10_L2.0-W2.0-P0.50-BL; LCSC C5124834; not fitted
U16: LIS3MDL; LGA-12_L2.0-W2.0-P0.50-BL; LCSC C478483
U17: ADXL375; LGA-14_L5.0-W3.0-P0.80-BL-1; LCSC C579466; not fitted
U18: SHT40-AD1B; DFN-4_L1.5-W1.5-P0.8-TL-EP; LCSC C2848306

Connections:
3V3: C47.1, C49.1, C50.1, C51.1, J12.2, R20.1, R21.1, U16.5 (Vdd), U16.6 (Vdd_IO), U16.9 (SD0/SA1), U16.10 (CS), U17.1 (VDDI/O), U17.6 (VS), U17.7 (~CS), U18.3 (VDD); also elsewhere on the board
3V3_SENS: C26.1, C27.1, C28.1, C29.1, C30.1, C31.1, C32.1, U4.5 (Vdd_IO), U4.8 (Vdd), U5.1 (VDDIO), U5.10 (VDD), U15.1 (VDDIO), U15.10 (VDD); also elsewhere on the board
CS_BARO: U5.6 (CSB); also elsewhere on the board
CS_BARO2: U15.6 (CSB); also elsewhere on the board
CS_IMU: U4.12 (CS); also elsewhere on the board
GND: C26.2, C27.2, C28.2, C29.2, C30.2, C31.2, C32.2, C47.2, C48.2, C49.2, C50.2, C51.2, J12.1, U4.2 (SDx/AH1/Qvar1), U4.3 (SCx/AH2/Qvar2), U4.6 (GND), U4.7 (GND), U5.3 (VSS), U5.8 (VSS), U5.9 (VSS), U15.3 (VSS), U15.8 (VSS), U15.9 (VSS), U16.2 (Res), U16.3 (GND), U16.12 (Res), U17.2 (GND), U17.3 (RESERVED), U17.4 (GND), U17.5 (GND), U17.11 (RESERVED), U17.12 (SDO/ALTADDRESS), U18.4 (VSS); also elsewhere on the board
IMU_INT: U4.4 (INT1); also elsewhere on the board
MAG_C1: C48.1, U16.4 (C1)
SCL: J12.4, R21.2, U16.1 (SCL/SPC), U17.14 (SCL/SCLK), U18.2 (SCL); also elsewhere on the board
SDA: J12.3, R20.2, U16.11 (SDA/SDI/SDO), U17.13 (SDA/SDI/SDIO), U18.1 (SDA); also elsewhere on the board
SPI1_MISO: U4.1 (SDO/SA0), U5.5 (SDO), U15.5 (SDO); also elsewhere on the board
SPI1_MOSI: U4.14 (SDA), U5.4 (SDI), U15.4 (SDI); also elsewhere on the board
SPI1_SCK: U4.13 (SCL), U5.2 (SCK), U15.2 (SCK); also elsewhere on the board

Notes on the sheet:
IMU LSM6DSV16X und zwei BMP390 an SPI1, I2C-Sensoren und Qwiic
IMU ICM-42688-P, SPI1
Barometer BMP390, SPI1
Qwiic, I2C
Magnetometer LIS3MDL, I2C (23.10.)
Feuchte und Temperatur SHT40, I2C (23.10.)
Hochbeschleunigung ADXL375, I2C, DNP (23.10.)

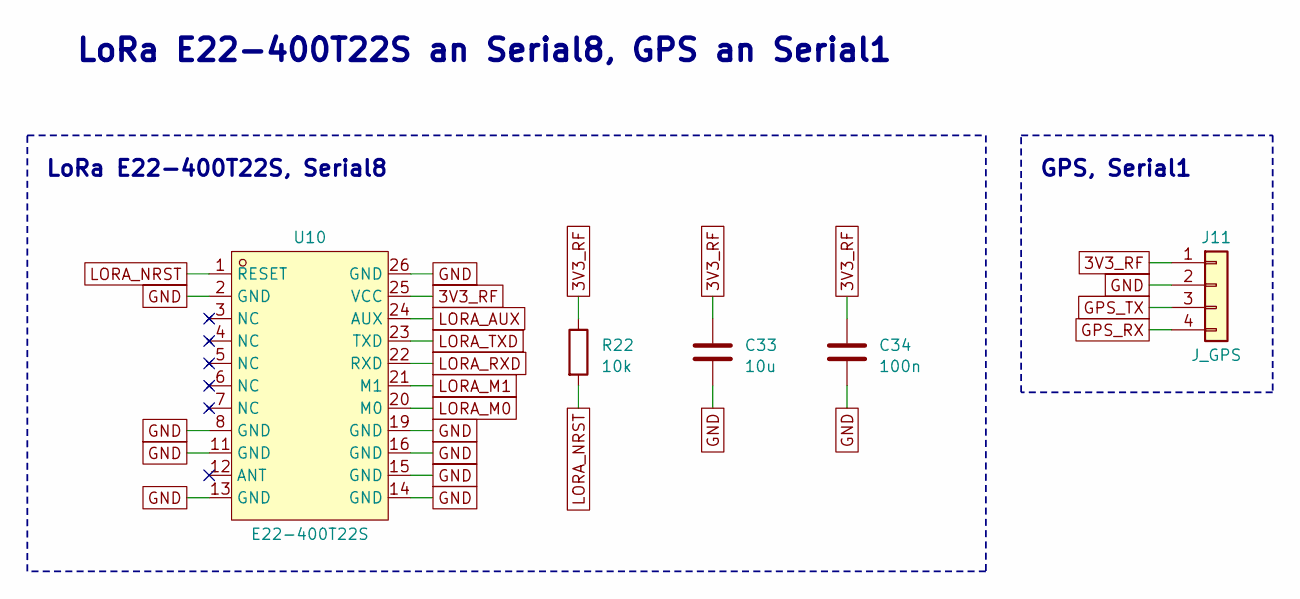
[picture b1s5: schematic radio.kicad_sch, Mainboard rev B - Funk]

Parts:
C33: 10u; C_0805_2012Metric
C34: 100n; C_0603_1608Metric
J11: J_GPS; JST_GH_BM04B-GHS-TBT_1x04-1MP_P1.25mm_Vertical
R22: 10k; R_0603_1608Metric
U10: E22-400T22S; WIRELM-SMD_E22-400T22S_1; LCSC C2903765

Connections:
3V3_RF: C33.1, C34.1, J11.1, R22.1, U10.25 (VCC); also elsewhere on the board
GND: C33.2, C34.2, J11.2, U10.2 (GND), U10.8 (GND), U10.11 (GND), U10.13 (GND), U10.14 (GND), U10.15 (GND), U10.16 (GND), U10.19 (GND), U10.26 (GND); also elsewhere on the board
GPS_RX: J11.4; also elsewhere on the board
GPS_TX: J11.3; also elsewhere on the board
LORA_AUX: U10.24 (AUX); also elsewhere on the board
LORA_M0: U10.20 (M0); also elsewhere on the board
LORA_M1: U10.21 (M1); also elsewhere on the board
LORA_NRST: R22.2, U10.1 (RESET); also elsewhere on the board
LORA_RXD: U10.22 (RXD); also elsewhere on the board
LORA_TXD: U10.23 (TXD); also elsewhere on the board

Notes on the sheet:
LoRa E22-400T22S an Serial8, GPS an Serial1
LoRa E22-400T22S, Serial8
GPS, Serial1
